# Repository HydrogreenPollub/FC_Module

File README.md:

View this project on [CADLAB.io](https://cadlab.io/project/29389). 

# FC_Module

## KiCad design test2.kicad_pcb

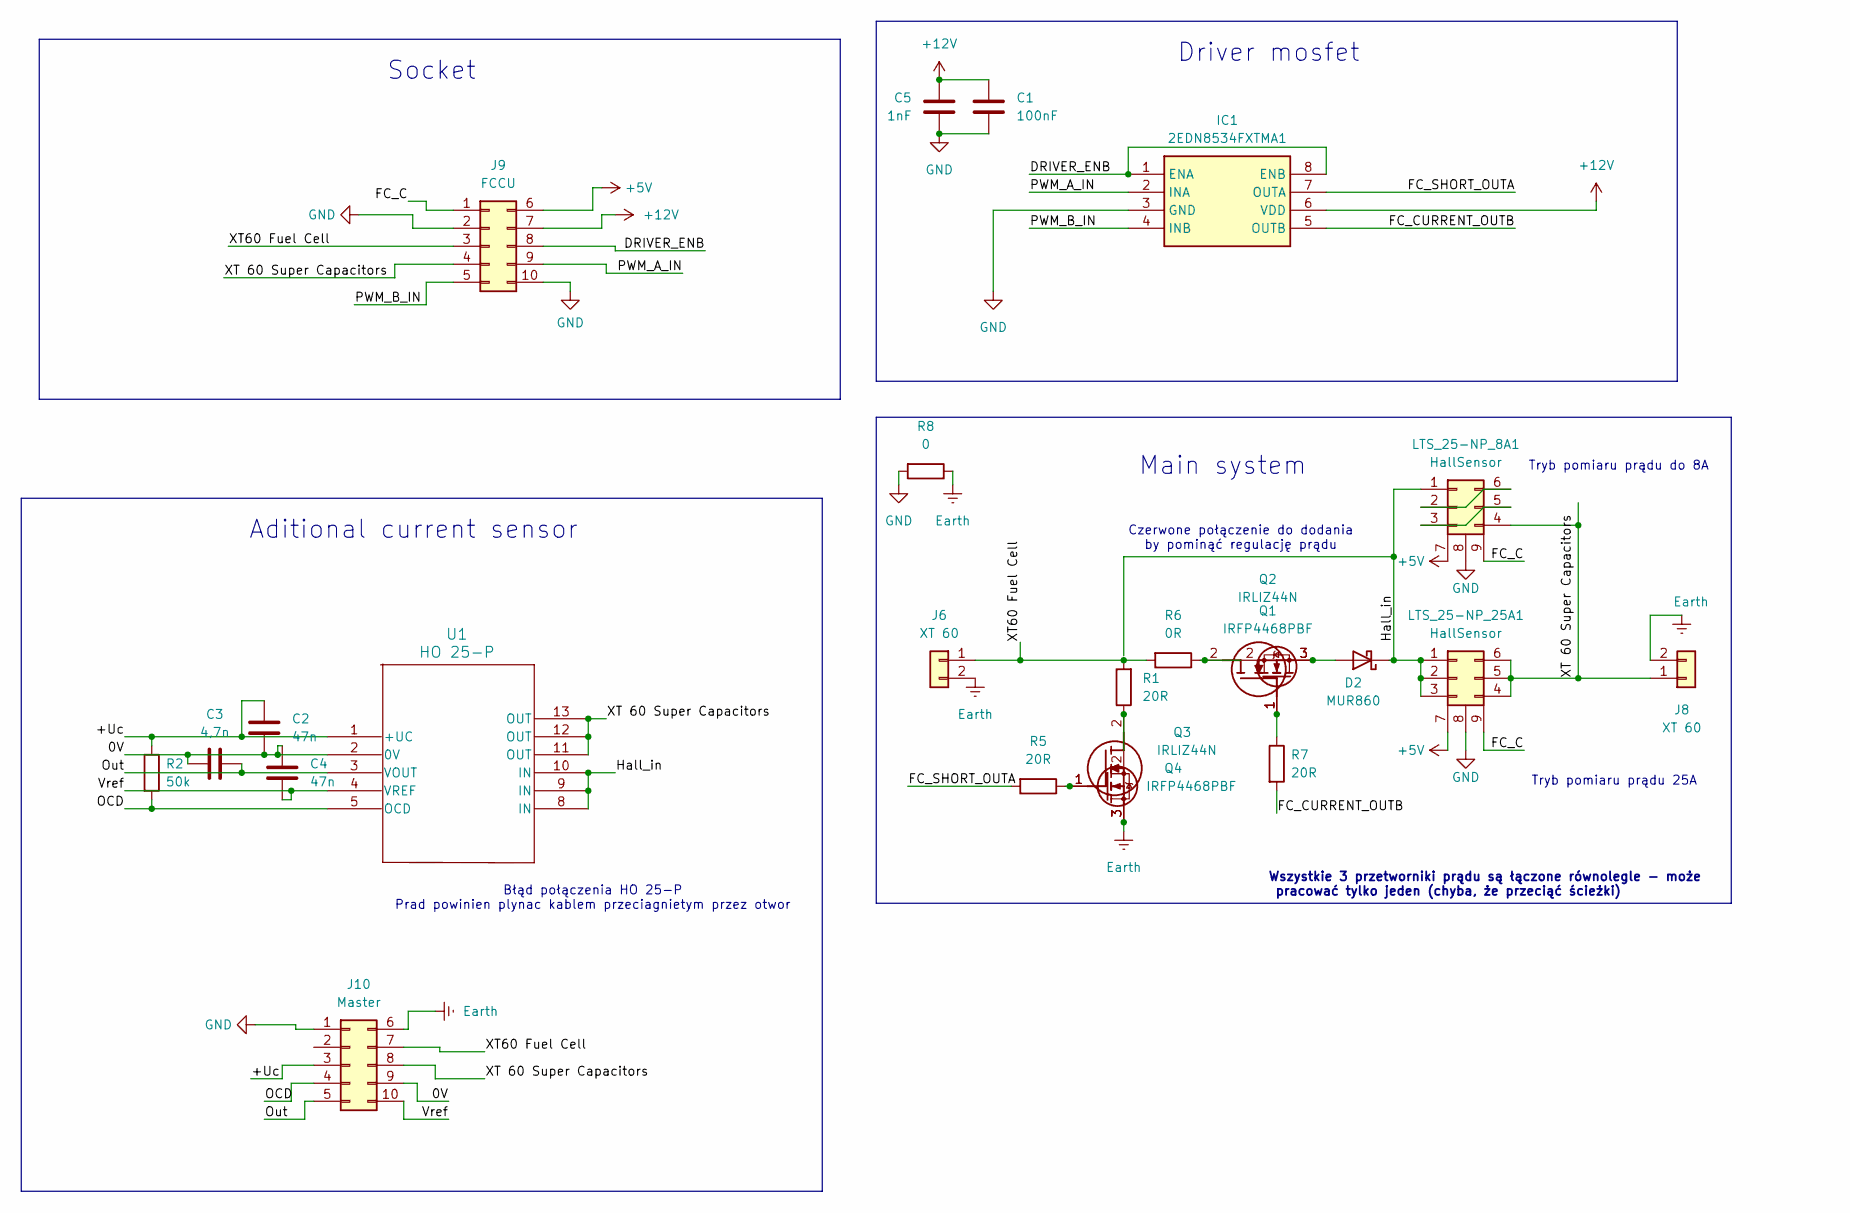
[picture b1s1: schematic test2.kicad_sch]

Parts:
C1: 100nF; C_1206_3216Metric_Pad1.33x1.80mm_HandSolder
C2, C4: 47n; C_1206_3216Metric
C3: 4,7n; C_1206_3216Metric
C5: 1nF; C_1206_3216Metric_Pad1.33x1.80mm_HandSolder
D2: MUR860; TO-220-2_Vertical
IC1: 2EDN8534FXTMA1; SOIC127P602X173-8N; Manufacturer_Part_Number 2EDN8534FXTMA1
J6, J8: XT 60; AMASS_XT60PW-M_1x02_P7.20mm_Horizontal
J9: FCCU; Molex_Mini-Fit_Jr_5569-10A1_2x05_P4.20mm_Horizontal
J10: Master; Molex_Mini-Fit_Jr_5569-10A1_2x05_P4.20mm_Horizontal
LTS_25-NP_8A1, LTS_25-NP_25A1: HallSensor; LTS-25-NP_1
Q1, Q4: IRFP4468PBF; TO546P531X1558X2499-3P; Mouser Part Number 942-IRFP4468PBF
Q2, Q3: IRLIZ44N; TO-220F-3_Vertical
R1: 20R; R_Axial_DIN0414_L11.9mm_D4.5mm_P7.62mm_Vertical
R2: 50k; R_1206_3216Metric
R5, R7: 20R; R_Axial_DIN0309_L9.0mm_D3.2mm_P5.08mm_Vertical
R6: 0R; R_Axial_DIN0309_L9.0mm_D3.2mm_P5.08mm_Vertical
R8: 0; R_Axial_DIN0309_L9.0mm_D3.2mm_P5.08mm_Vertical
U1: HO 25-P; HO 25-P_LEM

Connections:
+5V: J9.6, LTS_25-NP_8A1.7 (OUT), LTS_25-NP_25A1.7 (OUT)
+12V: C1.1, C5.1, IC1.6 (VDD), J9.7
/0V: C2.2, C3.1, C4.1, J10.9, U1.2 (0V)
/+Uc: C2.1, J10.3, R2.1, U1.1 (+UC)
/DRIVER_ENB: IC1.1 (ENA), IC1.8 (ENB), J9.8
/FC_C: J9.1, LTS_25-NP_8A1.9 (+5V), LTS_25-NP_25A1.9 (+5V)
/FC_CURRENT_OUTB: IC1.5 (OUTB), R7.2
/FC_SHORT_OUTA: IC1.7 (OUTA), R5.2
/Hall_in: D2.1 (K), LTS_25-NP_8A1.1, LTS_25-NP_25A1.1, LTS_25-NP_25A1.2, LTS_25-NP_25A1.3, U1.8 (IN), U1.9 (IN), U1.10 (IN)
/OCD: J10.4, R2.2, U1.5 (OCD)
/Out: C3.2, J10.5, U1.3 (VOUT)
/PWM_A_IN: IC1.2 (INA), J9.9
/PWM_B_IN: IC1.4 (INB), J9.5
/Vref: C4.2, J10.10, U1.4 (VREF)
/XT60 Fuel Cell: J6.1, J9.3, J10.7, R1.2, R6.2
/XT 60 Super Capacitors: J8.1, J9.4, J10.8, LTS_25-NP_8A1.4, LTS_25-NP_25A1.4, LTS_25-NP_25A1.5, LTS_25-NP_25A1.6, U1.11 (OUT), U1.12 (OUT), U1.13 (OUT)
Earth: J6.2, J8.2, J10.6, Q3.3 (S), Q4.3 (S), R8.1
GND: C1.2, C5.2, IC1.3 (GND), J9.2, J9.10, J10.1, LTS_25-NP_8A1.8 (0V), LTS_25-NP_25A1.8 (0V), R8.2
unnamed: D2.2 (A), Q1.3 (S), Q2.3 (S)
unnamed: LTS_25-NP_8A1.2, LTS_25-NP_8A1.6
unnamed: LTS_25-NP_8A1.3, LTS_25-NP_8A1.5
unnamed: Q1.2 (D), Q2.2 (D), R6.1
unnamed: Q1.1 (G), Q2.1 (G), R7.1
unnamed: Q3.2 (D), Q4.2 (D), R1.1
unnamed: Q3.1 (G), Q4.1 (G), R5.1

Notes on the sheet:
Socket
Tryb pomiaru prądu do 8A
Main system
Driver mosfet
Wszystkie 3 przetworniki prądu są łączone równolegle - może pracować tylko jeden (chyba, że przeciąć ścieżki)
Tryb pomiaru prądu 25A
Błąd połączenia HO 25-P Prad powinien plynac kablem przeciagnietym przez otwor
Czerwone połączenie do dodania by pominąć regulację prądu
Aditional current sensor

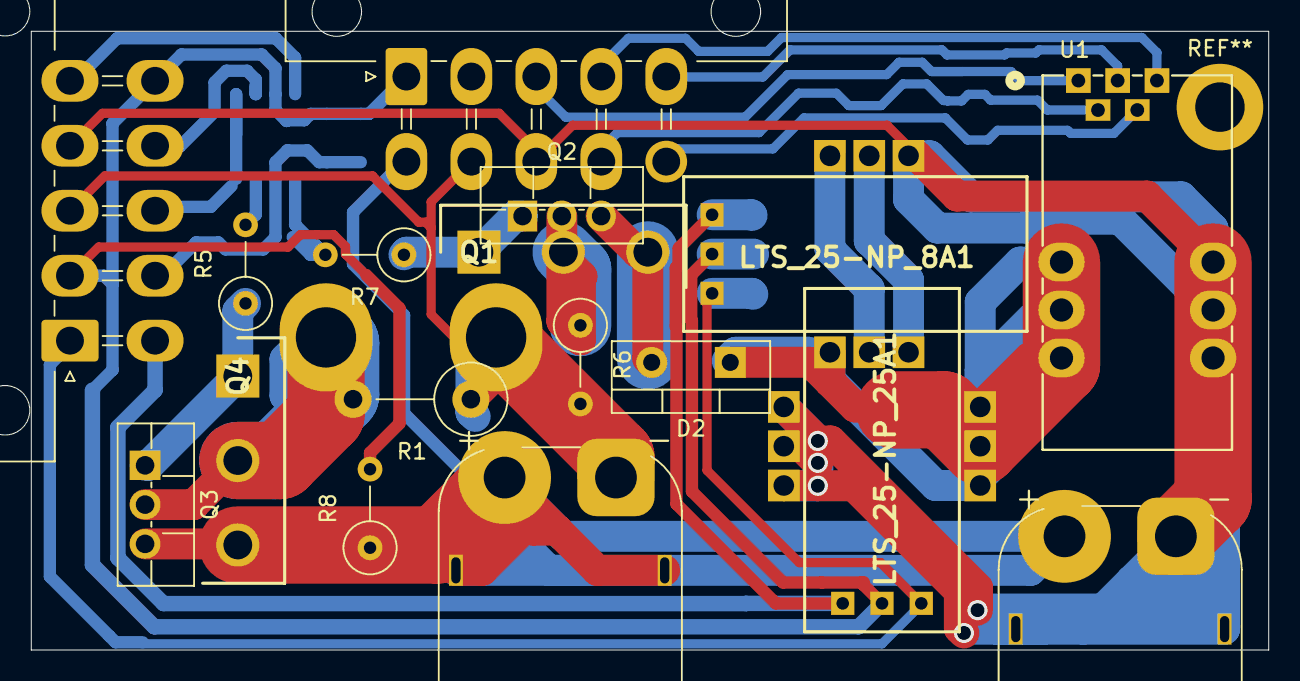
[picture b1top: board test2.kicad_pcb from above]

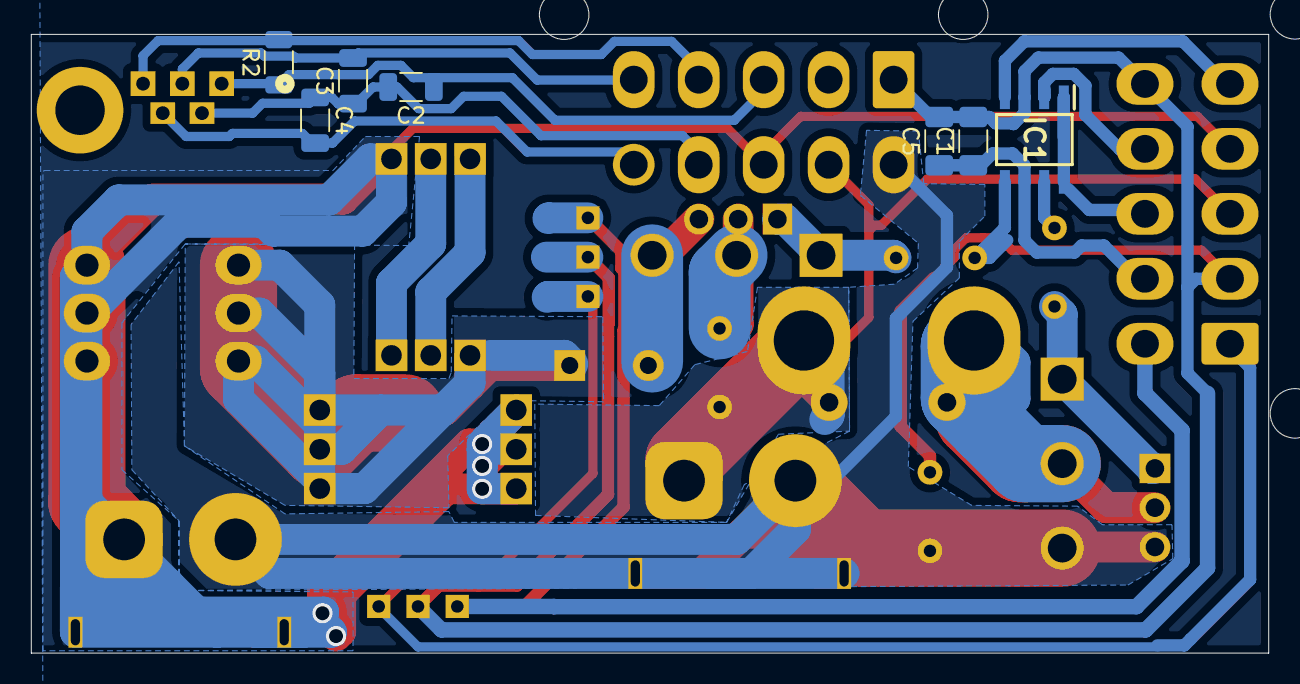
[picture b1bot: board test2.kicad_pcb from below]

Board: 2 copper layers, 80.0 x 40.0 mm, 24 parts (7 on the bottom side), 25 nets.

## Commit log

2025-05-22 Backlink to CADLAB.io has been added.
2025-05-23 Add 3d models
2025-05-27 Edit schema
